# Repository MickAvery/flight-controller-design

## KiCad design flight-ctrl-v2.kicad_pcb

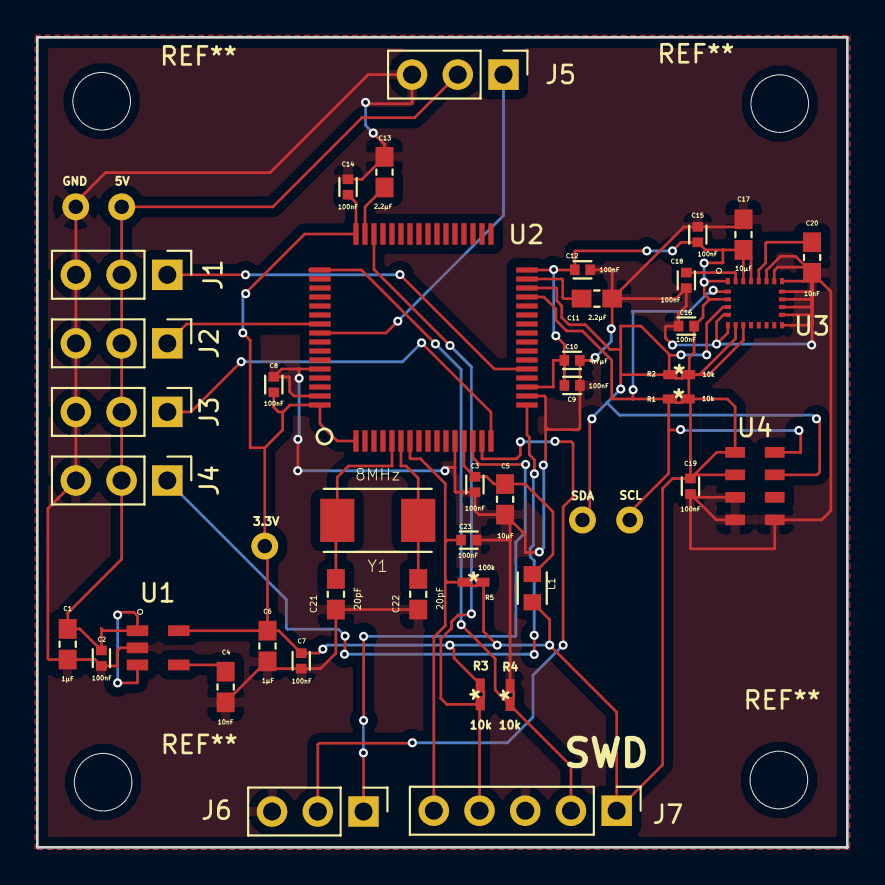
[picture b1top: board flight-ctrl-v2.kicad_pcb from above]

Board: 2 copper layers, 45.0 x 45.0 mm, 46 parts (0 on the bottom side), 23 nets.

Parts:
3.3V, 5V: TEST; Measurement_Point_Round-TH_Small
C1, C6: 1μF; CAPC1608X90
C2, C3, C7, C8, C9, C12, C14, C15, C16, C18, C19, C23: 100nF; CAPC1005X55N
C4, C20: 10nF; CAPC1608X90
C5, C17: 10μF; CAPC1608X90
C10: 4.7μF; CAPC1005X55N
C11, C13: 2.2μF; CAPC1608X90
C21, C22: 20pF; CAPC1608X90
GND: TEST; Measurement_Point_Round-TH_Small
J1: ESC1; Pin_Header_Straight_1x03_Pitch2.54mm
J2: ESC2; Pin_Header_Straight_1x03_Pitch2.54mm
J3: ESC3; Pin_Header_Straight_1x03_Pitch2.54mm
J4: ESC4; Pin_Header_Straight_1x03_Pitch2.54mm
J5: RECEIVER; Pin_Header_Straight_1x03_Pitch2.54mm
J6: SERIAL; Pin_Header_Straight_1x03_Pitch2.54mm
J7: SWD; Pin_Header_Straight_1x05_Pitch2.54mm
L1: BK1608HS601-T; BEADC1608X95N
R1, R2, R3, R4: 10k; RC0402FR-0710KL
R5: 100k; RC0402FR-07100KL
SCL: TEST; Measurement_Point_Round-TH_Small
SDA: TEST; Measurement_Point_Round-TH_Small
U1: LD3985M33R; LD3985MxxR
U2: STM32F405RG-LQFP64; STM32F405RxTx-LQFP64
U3: LSM9DS1
U4: MS5607; MS5607-02BA03
Y1: 8MHz; XTAL_ECS-080-18-23G-JGN-TR

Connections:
+3V3: 3.3V.1, C6.1, C7.1, C8.1, C9.1, C10.1, C12.1, C14.1, C15.1, C16.1, C17.1, C19.1, J7.1, L1.2, R1.1, R2.1, R3.1, R5.1, U1.5, U2.1, U2.19, U2.32, U2.48, U2.64, U3.1, U3.3, U3.7, U3.8, U3.22, U3.23, U4.1, U4.2
+5V: 5V.1, C1.1, C2.1, J1.2, J2.2, J3.2, J4.2, J5.2, U1.1, U1.3
GND: C1.2, C2.2, C3.2, C4.2, C5.2, C6.2, C7.2, C8.2, C9.2, C10.2, C11.2, C12.2, C13.2, C14.2, C15.2, C16.2, C17.2, C18.2, C19.2, C20.1, C21.1, C22.1, C23.2, GND.1, J1.3, J2.3, J3.3, J4.3, J5.3, J6.3, J7.3, R4.2, U1.2, U2.12, U2.18, U2.60, U2.63, U3.5, U3.6, U3.13, U3.14, U3.15, U3.16, U3.17, U3.18, U3.19, U3.20, U4.3, U4.4, U4.5
I2C2_SCL: R1.2, SCL.1, U2.29, U3.2, U4.8
I2C2_SDA: R2.2, SDA.1, U2.30, U3.4, U4.7
unnamed: C3.1, C5.1, L1.1, U2.13
unnamed: C4.1, U1.4
unnamed: C11.1, U2.31
unnamed: C13.1, U2.47
unnamed: C18.1, U3.24
unnamed: C20.2, U3.21
unnamed: C21.2, U2.5, Y1.2
unnamed: C22.2, U2.6, Y1.1
RESET: C23.1, J7.5, R5.2, U2.7
SWCLK: J7.2, R4.1, U2.49
SWDIO: J7.4, R3.2, U2.46
TIM2_CH1: J1.1, U2.21
TIM2_CH2: J2.1, U2.55
TIM2_CH3: J3.1, U2.16
TIM2_CH4: J4.1, U2.17
TIM3_CH1: J5.1, U2.56
UART4_RX: J6.2, U2.15
UART4_TX: J6.1, U2.14

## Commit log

2019-12-17 added pullup and pulldown resistors in schematic for SWD interface
2019-12-17 added swd resistors to pcb
2019-12-18 added ferrite bead as filter for VDDA
2019-12-18 deleted markers
2019-12-18 updated schematic pdf
2019-12-19 connected VBAT to VDD instead of GND

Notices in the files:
parts and their libraries:
Copyright 2016 Accelerated Designs. All rights reserved.
